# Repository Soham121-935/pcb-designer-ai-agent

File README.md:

# PCB Design AI Agent

An AI agent for **real KiCad PCB engineering work**: inspect a board, plan a change, execute it
through a typed tool layer, re-parse the result, validate it, and report what actually happened.

This repository is being repaired in phases. The current state is **Phase 2** — the existing system is
reproducible, its tools report failures honestly, and a repo-level agent tool surface exists.
The board *model* (parser), *controlled modification* and *DRC* are Phase 4-6 and are **not** implemented
yet; where a capability is missing the tool layer says so instead of improvising.

Read [`docs/AUDIT.md`](docs/AUDIT.md) for the full audit, the defect register and the locked decisions.

---

## Quick start

```bash
./scripts/bootstrap.sh        # .venv + deps. No uv, no KiCad, no API keys required.
make test                     # 63 tests, all runnable offline and without KiCad
make tools                    # every tool + its safety class + maturity
make backend                  # which EDA backends are usable here
make demo                     # requirements → BOM → footprint → pipeline (reports mode)
make rpc                      # drive the Anna JSON-RPC plugin over stdio
```

Invoke a single tool (this is exactly what the agent does):

```bash
export PYTHONPATH=anna-app/executas/pcb-designer

.venv/bin/python -m pcbai.agent.cli call capabilities

.venv/bin/python -m pcbai.agent.cli call generate_footprint --confirm \
  --arg footprint_type=qfp \
  --json '{"params":{"name":"LQFP-144_TQFP_20x20_P0.5","pins":144,"pitch":0.5,
          "body_l":20,"body_w":20,"pad_l":1.2,"pad_w":0.25}}'

.venv/bin/python -m pcbai.agent.cli call inspect_pcb_file \
  --json '{"path":"anna-app/executas/pcb-designer/pcbai/steps/template_project/board.kicad_pcb"}'
```

`call` exits non-zero whenever a tool returns `success: false`, so it is safe to script.

### System requirements

| Requirement | Needed for | Notes |
|---|---|---|
| Python ≥ 3.10, `click`, `requests` | everything in the repo | installed by `bootstrap.sh` |
| `pypdf` **or** `pdfminer.six` | `extract_package_from_pdf` | datasheet text extraction |
| **KiCad ≥ 8 with python bindings + `kicad-cli`** | `route_pcb`, native board authoring, DRC/Gerber parity | **optional**; without it those tools return `success:false / reason:"backend-unavailable"` instead of silently "succeeding" |
| `skidl` | `pcbai synthesize` (CLI) | optional, not installed by default |
| `java` + `freerouting.jar` | Freerouting pass after `.dsn` export | optional |

KiCad is detected, never assumed. Override discovery with `PCB_AI_KICAD_LIB_PATH` (directory containing
`pcbnew`), `PCB_AI_KICAD_CLI`, `PCB_AI_KICAD_FOOTPRINT_DIR`, `PCB_AI_KICAD_PYTHON`.

---

## Architecture

```
 natural-language PCB task
          │
          ▼
   ┌──────────────────────────────────────────────────────────┐
   │  THE AGENT (me, Claude Code, in this repo)               │
   │  inspect → plan → mutate → re-parse → validate → report │
   └──────────────────────────────────────────────────────────┘
          │  typed tool calls (read-only | mutating+confirm)
          ▼
   pcbai/agent/registry.py ── dispatch() ── policy gates (§ safety below)
          │
          ▼
   pcbai/agent/tools.py  ──►  pcbai/steps/*      (pure-Python: footprints, BOM, extraction)
          │                   pcbai/core/filesafe (backup → atomic write → verify → rollback)
          │                   pcbai/eda/backend   (KiCad capability probe)
          ▼
   pcbai/steps/pcb_router.py ──► KiCad pcbnew (child process) ── optional Freerouting
   pcbai/steps/gerber_exporter.py ──► kicad-cli

   Anna OS path (secondary, unchanged contract): anna-app/bundle/app.js
      → Anna host agent → JSON-RPC over stdio → anna-app/executas/pcb-designer/plugin.py
        (7 tools; reverse-RPC `sampling/createMessage` borrows Anna's LLM)
```

* **`pcbai` is one package, not two.** It physically lives in
  `anna-app/executas/pcb-designer/pcbai/` so the Anna plugin keeps its layout; the root
  `pyproject.toml` maps `package-dir = {"" = "anna-app/executas/pcb-designer"}` and
  `[tool.pytest.ini_options] pythonpath` makes it importable from the repo root with no install step.
* **There is no LLM tool-calling loop in the repo yet** (Phase 3). The `LLMProvider` layer is
  text-in/text-out; only two steps use it (`parse_requirements`, the pipeline report). Until Phase 3,
  *the agent* is the planner and calls the tools directly — which is why the tool layer, not the
  prompt, carries the safety guarantees.

### Target CAD format

KiCad S-expressions, **emitting KiCad 10** (`(version 20260206)`, `(generator_version "10.0")`) and
reading KiCad 7→10 (decided in AUDIT §11/Q3). Known deviation: the footprint writers still emit the
KiCad 5/6 `module`/`fp_text` dialect and say so in `warnings` — upgrading them is part of the
Phase 4/5 writer work, not silently pretending they are KiCad 10.

Manufacturing-target defaults are **not** fixed yet (AUDIT §11/Q4). When they are, they land as an
editable per-project rules file, not constants.

---

## Tool surface (as implemented, not as advertised)

Legend: **usable** now · **placeholder** returns data that is not engineering-grade ·
**Phase N** registered but refuses with `reason:"not-implemented"`.

| Tool | Safety | State | What it really does |
|---|---|---|---|
| `capabilities` | read-only | usable | pcbnew / kicad-cli / footprint libs / Freerouting availability + notes |
| `list_project_files` | read-only | usable | finds `.kicad_pcb/.kicad_sch/.kicad_pro/.kicad_mod/bom` under a project dir |
| `read_project_file` | read-only | usable | size-capped read, refuses paths escaping the project root |
| `inspect_pcb_file` | read-only | usable | depth-aware top-level counts (footprints, pads, segments, vias, zones, Edge.Cuts, net table, net classes) + structural warnings. **Counts only — no geometry yet** |
| `extract_package_from_pdf` | read-only | usable (weak) | regex/keyword extraction from datasheet text; unresolved fields are listed in `warnings` |
| `generate_bom` | read-only | usable (limited) | maps keywords to a 12-part built-in catalog; unmatched keywords → `*-UNKNOWN` + warning. **No vendor/stock lookup** |
| `parse_requirements` | read-only | usable | LLM → JSON, deterministic keyword fallback (reported as `source:"keyword-fallback"`) |
| `synthesize_netlist` | read-only | **placeholder** | GND/VCC ref groups, *no REF-PIN connectivity* → a router cannot use it (Phase 4) |
| `generate_footprint` | mutating | usable | 9 package types; writes `<project>/footprints/*.kicad_mod`, **re-reads and compares**, validates paren balance + pad count |
| `create_backup` | mutating | usable | explicit `.bak` + append-only `.history/` snapshot |
| `route_pcb` | mutating | usable only with KiCad | loads `footprints/`, assigns pads→nets, heuristic placement, `.dsn` export, optional Freerouting; honest `ok/reason` |
| `full_pipeline` | mutating | usable | requirements → BOM → board. `data.mode` = `generated` \| `template`; template results are flagged `template_only:true` with warnings |
| `inspect_project`, `inspect_pcb`, `inspect_schematic`, `list_components`, `get_component`, `get_nets`, `get_board_outline`, `get_design_rules` | read-only | **Phase 4** | refused: `not-implemented` |
| `add_component`, `remove_component`, `move_component`, `rotate_component`, `set_footprint`, `add_track`, `add_via`, `route_net`, `set_board_outline`, `save_project` | mutating | **Phase 5** | refused: `not-implemented` |
| `run_drc`, `run_erc`, `validate_project`, BOM↔schematic consistency, fab checks | read-only | **Phase 6** | refused: `not-implemented` |

`pcbai-agent tools` prints this live; `pcbai-agent describe <tool>` shows parameters.

### Safety model (enforced in code, `pcbai/agent/registry.py`)

1. Every tool is classified **read-only** or **mutating**.
2. Mutating tools are refused unless the caller passes `confirm=True` (`reason:"needs-confirmation"`)
   and are blocked entirely by `--no-mutating` (`reason:"needs-mutation-approval"`).
3. Writes go through `pcbai/core/filesafe.py`: backup → temp file + `fsync` + `os.replace` →
   re-read/validate → **rollback on failure**; `.history/` keeps one entry per overwrite;
   non-PCB extensions and `*.bak`/`.history` paths are rejected; a transaction cannot escape its root.
4. `success:true` means the **post-condition was verified**, not that a file was written.
5. Missing capabilities are reported as `skipped`/`not-implemented` with a reason — never as a pass.

---

## Workflow the agent must follow

```
inspect project → inspect board → plan → (backup) → mutate → re-parse → validate → DRC/ERC (if KiCad)
                                                          → inspect result → fix → report what changed
```
Ambiguous engineering requests ("make the power section better") must produce an inspection report
plus a clarifying question, not a guessed edit. Deterministic requests ("move R12 5 mm left") execute.

---

## Environment variables

| Variable | Default | Meaning |
|---|---|---|
| `PCB_AI_LLM_PROVIDER` | `openai` (plugin: host sampling when unset/`anna`) | `openai`\|`gemini`\|`claude`/`anthropic`\|`ollama`\|`lmstudio`\|`dummy` |
| `PCB_AI_MODEL` | provider-specific | model id for any provider |
| `OPENAI_API_KEY` / `GEMINI_API_KEY` / `ANTHROPIC_API_KEY` | — | provider keys |
| `LMSTUDIO_URL` / `OLLAMA_URL` / `OLLAMA_HOST` | `http://localhost:1234` / `:11434` | local endpoints |
| `PCB_AI_MAX_TOKENS`, `PCB_AI_TEMPERATURE` | call-site value | override all LLM calls |
| `PCB_AI_SAMPLE_TIMEOUT` | `60` | seconds to wait for Anna reverse-RPC sampling |
| `PCB_AI_WORKDIR` | `<repo>/build` | generated output root |
| `PCB_AI_PROJECT` | `$PCB_AI_WORKDIR/demo-project` | project dir the tools read/write |
| `PCB_AI_REPO_ROOT` | auto-detected | override repo-root discovery |
| `PCB_AI_ALLOW_TEMPLATE_COPY` | `1` | permit the ESP32-C3 reference-template fallback (always reported as `mode:"template"`) |
| `PCB_AI_EXPERIMENTAL_ROUTER` | `0` | enable the naive Manhattan router (**produces shorts**; not for real work) |
| `PCB_AI_KICAD_LIB_PATH` | distro paths | dirs to search for `pcbnew` |
| `PCB_AI_KICAD_PYTHON` | `python3` | interpreter that can import `pcbnew` |
| `PCB_AI_KICAD_CLI` (legacy `KICAD_CLI`) | `kicad-cli` | for Gerber/parity checks |
| `PCB_AI_KICAD_FOOTPRINT_DIR`, `PCB_AI_KICAD_SYMBOL_DIR` | `/usr/share/kicad/...` | KiCad libraries |
| `PCB_AI_FREEROUTING_JAR`, `PCB_AI_JAVA` | — | DSN→SES routing pass |
| `PCB_AI_LOG` | `INFO` | log level (stderr only) |
| `OCTOPART_API_KEY` | — | **declared in `executa.json` but not implemented**; nothing reads it |

---

## Testing

```bash
make test                                   # 63 tests, no KiCad / no network
cd anna-app/executas/pcb-designer && PCB_AI_LLM_PROVIDER=dummy python3 test_harness.py --smoke
python3 -m pytest tests/test_rpc_protocol.py -q      # JSON-RPC contract + honesty invariants
```

CI (`.github/workflows/ci.yml`) runs two lanes: **core** (must pass with no KiCad) and
**kicad-parity** (`kicad/kicad:latest` container) which exercises the same assertions where a real
`pcbnew`/`kicad-cli` exists. Test suite layout: parser/tool layer (`test_tool_layer.py`),
file safety (`test_filesafe.py`), pipeline honesty (`test_design_compiler.py`), router contract
(`test_pcb_router.py`), RPC protocol (`test_rpc_protocol.py`), plus the inherited footprint/datasheet
tests in `tests/test_*.py`.

---

## Known limitations (current, real)

1. **No board model.** Nothing can read a `.kicad_pcb`/`.kicad_sch` into geometry — `inspect_pcb_file`
   is a structural sanity check only. "Move C12", "route this net", "run DRC" are impossible today.
2. **Netlists have no pad-level connectivity** (`schematic_synthesizer` is a placeholder), so routing
   has no input even when KiCad is installed.
3. **No DRC/ERC/fab checks** in the agent path; `kicad-cli` parity checks are not wired yet.
4. **`full_pipeline` does not design.** It returns a hardcoded ESP32-C3 reference board unless KiCad's
   writers run (which are themselves hardcoded to that board). Now labelled `mode:"template"`.
5. **Footprint dialect** is KiCad 5/6 `module`/`fp_text` — loads in modern KiCad after an upgrade
   pass, but is not KiCad 10 native. Flagged in every tool warning.
6. **`bom_generator` catalog is 12 hardcoded parts**; no vendor, price, stock, or lifecycle data.
7. **Datasheet extraction is weak**: on the bundled 2 MB LM5164 PDF it recovers only `soic`/`8 pins`
   and leaves pitch/body/pad dimensions null.
8. **The Anna web UI can still fabricate PCB files in the browser** when tool output lacks fields
   (`anna-app/bundle/app.js`) — scheduled for removal so the UI only shows validated artifacts.
9. **No LLM tool loop in-repo** (Phase 3); `plugin.py`'s reverse-RPC sampling needs a host that answers
   `sampling/createMessage` (the local `test_harness.py` does).
10. The bundled **`pcb_project.zip` is stale** relative to the template files inside
    `template_project/` (regenerate before shipping it).

## Contributing / roadmap

Phase 3 agent loop → Phase 4 KiCad parser + board model → Phase 5 validated mutation + router →
Phase 6 DRC/ERC/fab checks → Phase 7 orchestration → Phase 8 test hardening → Phase 9 SV-16 board.
Full details and commit plan: [`docs/AUDIT.md`](docs/AUDIT.md) §9.

## License

Dual-licensed: non-commercial open source under `LICENSE`; commercial/enterprise use requires prior
written authorisation from the author (contact in `LICENSE`). This is inherited from the upstream
project — confirm the licence fits your intended use before relying on it.

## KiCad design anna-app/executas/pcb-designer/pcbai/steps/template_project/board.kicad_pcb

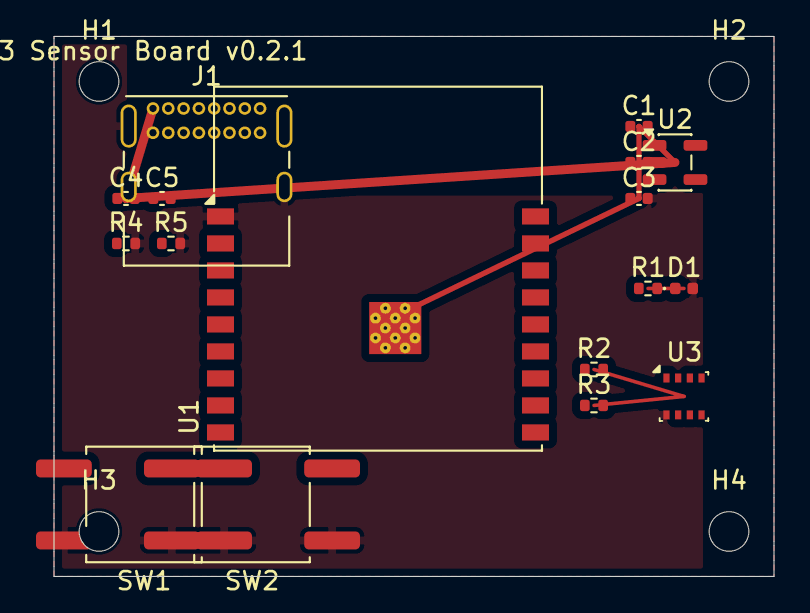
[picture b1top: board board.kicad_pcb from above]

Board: 2 copper layers, 40.0 x 30.0 mm, 21 parts (0 on the bottom side), 12 nets.

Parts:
C1, C2, C4, C5: 100nF; C_0402_1005Metric
C3: 10uF; C_0402_1005Metric
D1: APHHS1005CGCK; LED_0402_1005Metric
H1, H2, H3, H4: M2; MountingHole_2.2mm_M2_DIN965
J1: USB4085-GF-A; USB_C_Receptacle_GCT_USB4085
R1: 330R; R_0402_1005Metric
R2, R3: 4K7; R_0402_1005Metric
R4, R5: 5K1; R_0402_1005Metric
SW1: BOOT; SW_Push_1P1T_NO_CK_KSC9xxG
SW2: RESET; SW_Push_1P1T_NO_CK_KSC9xxG
U1: ESP32-C3-MINI-1; ESP32-C3-WROOM-02
U2: AP2112K-3.3TRG1; SOT-23-5
U3: BME280; Bosch_LGA-8_2.5x2.5mm_P0.65mm_ClockwisePinNumbering

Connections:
+3V3: C1.1, C2.1, C3.1, R1.1, R2.1, R3.1, U1.2, U2.5, U3.1, U3.7
BOOT_BTN: SW1.1, U1.11
CC1: J1.A5, R4.1
CC2: J1.B5, R5.1
GND: C1.2, C2.2, C3.2, C4.2, C5.2, D1.2, J1.A1, J1.A12, J1.B1, J1.B12, J1.SH, R4.2, R5.2, SW1.2, SW2.2, U1.1, U2.2, U3.2, U3.8
I2C_SCL: R2.2, U1.8, U3.6
I2C_SDA: R3.2, U1.9, U3.5
LED_ANODE: D1.1, R1.2
USB_DN: J1.A7, J1.B7, U1.18
USB_DP: J1.A6, J1.B6, U1.19
VBUS: C4.1, C5.1, J1.A4, J1.A9, J1.B4, J1.B9, U2.1
nRESET: SW2.1, U1.3

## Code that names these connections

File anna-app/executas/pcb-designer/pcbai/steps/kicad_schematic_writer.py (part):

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        _pin("GND",     2, -10.16,   7.62,   0,  "power_in") +
        _pin("EN",      3, -10.16,   5.08,   0,  "input") +
        _pin("GPIO9",   4, -10.16,   2.54,   0,  "bidirectional") +
        _pin("USB_DP",  5, -10.16,   0.00,   0,  "bidirectional") +
        _pin("USB_DN",  6, -10.16,  -2.54,   0,  "bidirectional") +
        _pin("GPIO6",   7,  10.16,   5.08, 180,  "bidirectional") +
        _pin("GPIO7",   8,  10.16,   2.54, 180,  "bidirectional") +
        _pin("GPIO8",   9,  10.16,   0.00, 180,  "bidirectional") +
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    lines.append(_label("VBUS",     70, 25))
    lines.append(_label("+3V3",     70, 34))
    lines.append(_label("+3V3",    113, 50))
    lines.append(_label("USB_DP",   55, 30))
    lines.append(_label("USB_DP",  113, 47))
    lines.append(_label("USB_DN",   55, 32))
    lines.append(_label("USB_DN",  113, 50))
    lines.append(_label("I2C_SCL", 113, 55))
    lines.append(_label("I2C_SCL", 163, 55))
    lines.append(_label("I2C_SDA", 113, 57))
    lines.append(_label("I2C_SDA", 163, 60))
    lines.append(_label("BOOT_BTN", 93, 90))
    lines.append(_label("BOOT_BTN", 113, 52))
    lines.append(_label("nRESET",  113, 50))
    lines.append(_label("nRESET",  113, 45))
    lines.append(_label("LED_NET", 143, 30))

    # ── Wires ─────────────────────────────────────────────────────────────────
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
